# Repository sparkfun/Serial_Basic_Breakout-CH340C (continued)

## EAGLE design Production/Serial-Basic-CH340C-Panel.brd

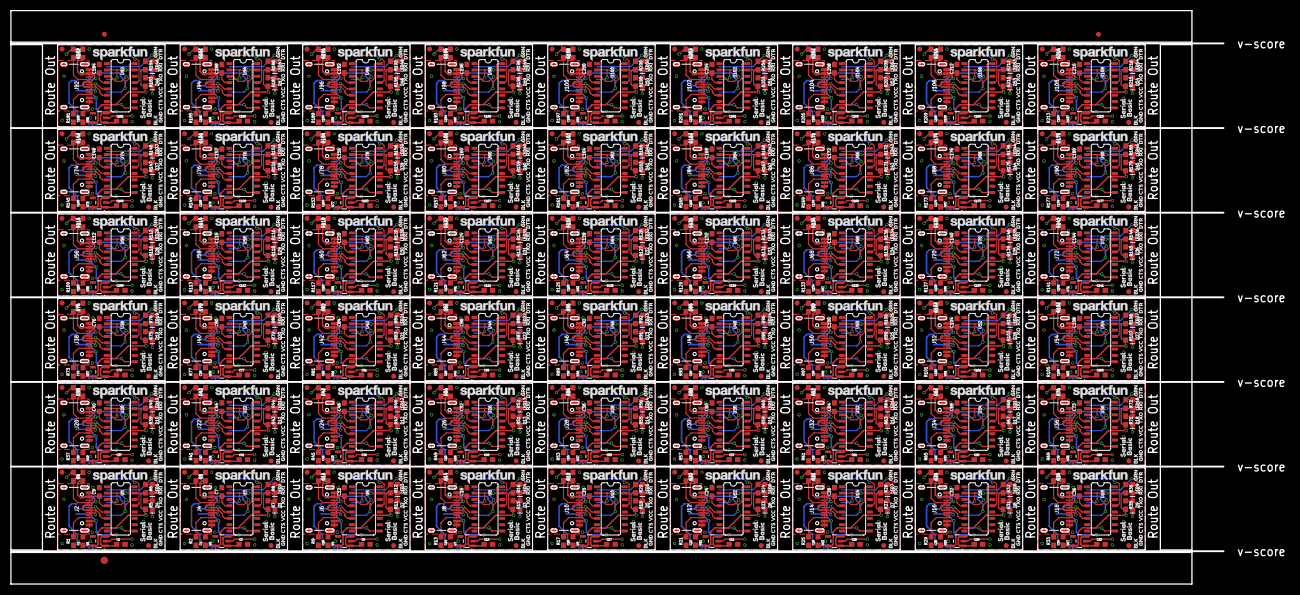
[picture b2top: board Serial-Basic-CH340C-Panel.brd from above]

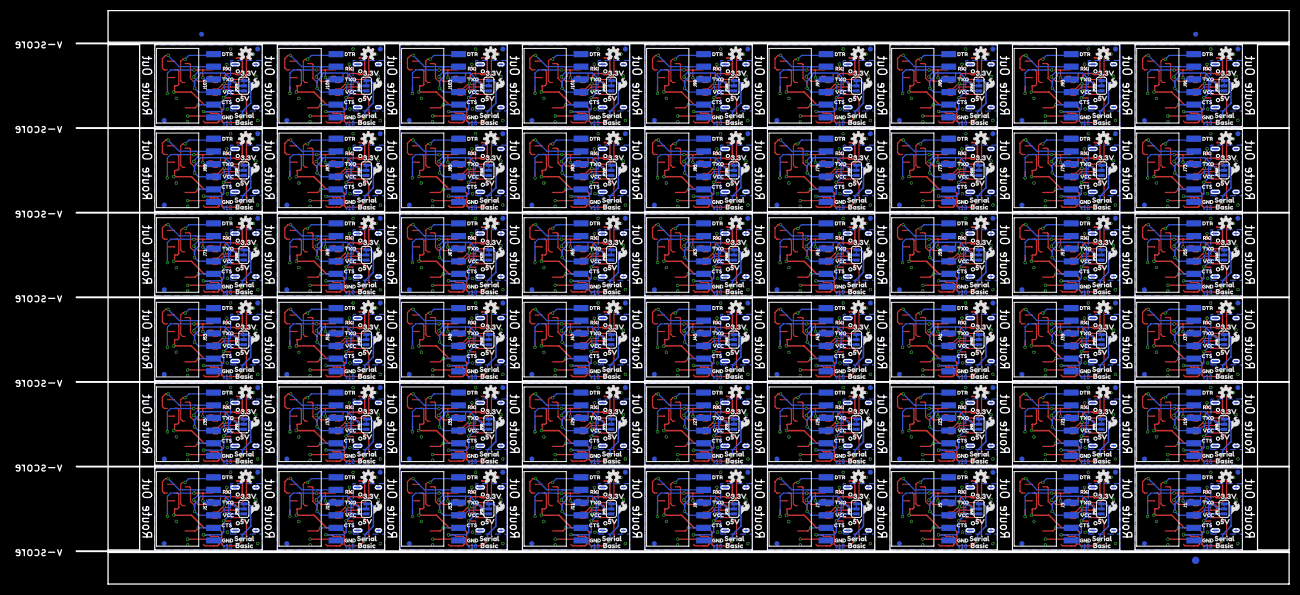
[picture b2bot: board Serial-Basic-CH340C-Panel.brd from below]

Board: 2 copper layers, 243.8 x 115.3 mm, 2274 parts (867 on the bottom side), 864 nets.

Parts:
C1, C2, C3, C4, C8, C10, C13, C14, C17, C18, C21, C22, C25, C26, C29, C30, C33, C34, C37, C38, C41, C42, C45, C46, C49, C50, C53, C54, C57, C58, C61, C62, C65, C66, C69, C70, C73, C74, C77, C78, C81, C82, C85, C86, C89, C90, C93, C94, C97, C98, C101, C102, C105, C106, C109, C110, C113, C114, C117, C118, C121, C122, C125, C126, C129, C130, C133, C134, C137, C138, C141, C142, C145, C146, C149, C150, C153, C154, C157, C158, C161, C162, C165, C166, C169, C170, C173, C174, C177, C178, C181, C182, C185, C186, C189, C190, C193, C194, C197, C198, C201, C202, C205, C206, C209, C210, C213, C214: 1.0uF; 0603
C5, C6, C11, C15, C19, C23, C27, C31, C35, C39, C43, C47, C51, C55, C59, C63, C67, C71, C75, C79, C83, C87, C91, C95, C99, C103, C107, C111, C115, C119, C123, C127, C131, C135, C139, C143, C147, C151, C155, C159, C163, C167, C171, C175, C179, C183, C187, C191, C195, C199, C203, C207, C211, C215: 0.1uF; 0603
C7, C9, C12, C16, C20, C24, C28, C32, C36, C40, C44, C48, C52, C56, C60, C64, C68, C72, C76, C80, C84, C88, C92, C96, C100, C104, C108, C112, C116, C120, C124, C128, C132, C136, C140, C144, C148, C152, C156, C160, C164, C168, C172, C176, C180, C184, C188, C192, C196, C200, C204, C208, C212, C216: 10nF; 0603
D1, D2, D3, D4, D5, D6, D7, D8, D9, D10, D11, D12, D13, D14, D15, D16, D17, D18, D19, D20, D21, D22, D23, D24, D25, D26, D27, D28, D29, D30, D31, D32, D33, D34, D35, D36, D37, D38, D39, D40, D41, D42, D43, D44, D45, D46, D47, D48, D49, D50, D51, D52, D53, D54: Yellow; LED-0603
E$1, E$2, E$3, E$4: FIDUCIAL-1X2
E$5, E$6: FIDUCIAL-1.5X3
J1, J3, J5, J7, J9, J11, J13, J15, J17, J19, J21, J23, J25, J27, J29, J31, J33, J35, J37, J39, J41, J43, J45, J47, J49, J51, J53, J55, J57, J59, J61, J63, J65, J67, J69, J71, J73, J75, J77, J79, J81, J83, J85, J87, J89, J91, J93, J95, J97, J99, J101, J103, J105, J107: 1X06-SMD-FEMALE
J2, J4, J6, J8, J10, J12, J14, J16, J18, J20, J22, J24, J26, J28, J30, J32, J34, J36, J38, J40, J42, J44, J46, J48, J50, J52, J54, J56, J58, J60, J62, J64, J66, J68, J70, J72, J74, J76, J78, J80, J82, J84, J86, J88, J90, J92, J94, J96, J98, J100, J102, J104, J106, J108: USB-C-16P
JP1, JP10, JP15, JP20, JP25, JP30, JP35, JP40, JP45, JP50, JP55, JP60, JP65, JP70, JP75, JP80, JP85, JP90, JP95, JP100, JP105, JP110, JP115, JP120, JP125, JP130, JP135, JP140, JP145, JP150, JP155, JP160, JP165, JP170, JP175, JP180, JP185, JP190, JP195, JP200, JP205, JP210, JP215, JP220, JP225, JP230, JP235, JP240, JP245, JP250, JP255, JP260, JP265, JP270: SMT-JUMPER_3_1-NC_TRACE_SILK
JP2, JP3, JP4, JP5, JP6, JP7, JP8, JP9, JP11, JP12, JP13, JP14, JP16, JP17, JP18, JP19, JP21, JP22, JP23, JP24, JP26, JP27, JP28, JP29, JP31, JP32, JP33, JP34, JP36, JP37, JP38, JP39, JP41, JP42, JP43, JP44, JP46, JP47, JP48, JP49, JP51, JP52, JP53, JP54, JP56, JP57, JP58, JP59, JP61, JP62, JP63, JP64, JP66, JP67, JP68, JP69, JP71, JP72, JP73, JP74, JP76, JP77, JP78, JP79, JP81, JP82, JP83, JP84, JP86, JP87, JP88, JP89, JP91, JP92, JP93, JP94, JP96, JP97, JP98, JP99, JP101, JP102, JP103, JP104, JP106, JP107, JP108, JP109, JP111, JP112, JP113, JP114, JP116, JP117, JP118, JP119, JP121, JP122, JP123, JP124, JP126, JP127, JP128, JP129, JP131, JP132, JP133, JP134, JP136, JP137, JP138, JP139, JP141, JP142, JP143, JP144, JP146, JP147, JP148, JP149, JP151, JP152, JP153, JP154, JP156, JP157, JP158, JP159, JP161, JP162, JP163, JP164, JP166, JP167, JP168, JP169, JP171, JP172, JP173, JP174, JP176, JP177, JP178, JP179, JP181, JP182, JP183, JP184, JP186, JP187, JP188, JP189, JP191, JP192, JP193, JP194, JP196, JP197, JP198, JP199, JP201, JP202, JP203, JP204, JP206, JP207, JP208, JP209, JP211, JP212, JP213, JP214, JP216, JP217, JP218, JP219, JP221, JP222, JP223, JP224, JP226, JP227, JP228, JP229, JP231, JP232, JP233, JP234, JP236, JP237, JP238, JP239, JP241, JP242, JP243, JP244, JP246, JP247, JP248, JP249, JP251, JP252, JP253, JP254, JP256, JP257, JP258, JP259, JP261, JP262, JP263, JP264, JP266, JP267, JP268, JP269: FIDUCIAL1X2; FIDUCIAL-1X2
LED1, LED2, LED3, LED4, LED5, LED6, LED7, LED8, LED9, LED10, LED11, LED12, LED13, LED14, LED15, LED16, LED17, LED18, LED19, LED20, LED21, LED22, LED23, LED24, LED25, LED26, LED27, LED28, LED29, LED30, LED31, LED32, LED33, LED34, LED35, LED36, LED37, LED38, LED39, LED40, LED41, LED42, LED43, LED44, LED45, LED46, LED47, LED48, LED49, LED50, LED51, LED52, LED53, LED54: GREEN; LED-0603
LOGO1, LOGO4, LOGO7, LOGO10, LOGO13, LOGO16, LOGO19, LOGO22, LOGO25, LOGO28, LOGO31, LOGO34, LOGO37, LOGO40, LOGO43, LOGO46, LOGO49, LOGO52, LOGO55, LOGO58, LOGO61, LOGO64, LOGO67, LOGO70, LOGO73, LOGO76, LOGO79, LOGO82, LOGO85, LOGO88, LOGO91, LOGO94, LOGO97, LOGO100, LOGO103, LOGO106, LOGO109, LOGO112, LOGO115, LOGO118, LOGO121, LOGO124, LOGO127, LOGO130, LOGO133, LOGO136, LOGO139, LOGO142, LOGO145, LOGO148, LOGO151, LOGO154, LOGO157, LOGO160: OSHW-LOGOS; OSHW-LOGO-S
LOGO2, LOGO5, LOGO8, LOGO11, LOGO14, LOGO17, LOGO20, LOGO23, LOGO26, LOGO29, LOGO32, LOGO35, LOGO38, LOGO41, LOGO44, LOGO47, LOGO50, LOGO53, LOGO56, LOGO59, LOGO62, LOGO65, LOGO68, LOGO71, LOGO74, LOGO77, LOGO80, LOGO83, LOGO86, LOGO89, LOGO92, LOGO95, LOGO98, LOGO101, LOGO104, LOGO107, LOGO110, LOGO113, LOGO116, LOGO119, LOGO122, LOGO125, LOGO128, LOGO131, LOGO134, LOGO137, LOGO140, LOGO143, LOGO146, LOGO149, LOGO152, LOGO155, LOGO158, LOGO161: SFE_LOGO_FLAME.1_INCH; SFE_LOGO_FLAME_.1
LOGO3, LOGO6, LOGO9, LOGO12, LOGO15, LOGO18, LOGO21, LOGO24, LOGO27, LOGO30, LOGO33, LOGO36, LOGO39, LOGO42, LOGO45, LOGO48, LOGO51, LOGO54, LOGO57, LOGO60, LOGO63, LOGO66, LOGO69, LOGO72, LOGO75, LOGO78, LOGO81, LOGO84, LOGO87, LOGO90, LOGO93, LOGO96, LOGO99, LOGO102, LOGO105, LOGO108, LOGO111, LOGO114, LOGO117, LOGO120, LOGO123, LOGO126, LOGO129, LOGO132, LOGO135, LOGO138, LOGO141, LOGO144, LOGO147, LOGO150, LOGO153, LOGO156, LOGO159, LOGO162: SFE_LOGO_NAME.1_INCH; SFE_LOGO_NAME_.1
R1, R2, R3, R4, R9, R10, R13, R14, R17, R18, R21, R22, R25, R26, R29, R30, R33, R34, R37, R38, R41, R42, R45, R46, R49, R50, R53, R54, R57, R58, R61, R62, R65, R66, R69, R70, R73, R74, R77, R78, R81, R82, R85, R86, R89, R90, R93, R94, R97, R98, R101, R102, R105, R106, R109, R110, R113, R114, R117, R118, R121, R122, R125, R126, R129, R130, R133, R134, R137, R138, R141, R142, R145, R146, R149, R150, R153, R154, R157, R158, R161, R162, R165, R166, R169, R170, R173, R174, R177, R178, R181, R182, R185, R186, R189, R190, R193, R194, R197, R198, R201, R202, R205, R206, R209, R210, R213, R214: 5.1k; 0603
R5, R6, R7, R8, R11, R12, R15, R16, R19, R20, R23, R24, R27, R28, R31, R32, R35, R36, R39, R40, R43, R44, R47, R48, R51, R52, R55, R56, R59, R60, R63, R64, R67, R68, R71, R72, R75, R76, R79, R80, R83, R84, R87, R88, R91, R92, R95, R96, R99, R100, R103, R104, R107, R108, R111, R112, R115, R116, R119, R120, R123, R124, R127, R128, R131, R132, R135, R136, R139, R140, R143, R144, R147, R148, R151, R152, R155, R156, R159, R160, R163, R164, R167, R168, R171, R172, R175, R176, R179, R180, R183, R184, R187, R188, R191, R192, R195, R196, R199, R200, R203, R204, R207, R208, R211, R212, R215, R216: 1k; 0603
U1, U2, U4, U7, U9, U11, U13, U15, U17, U19, U21, U23, U25, U27, U29, U31, U33, U35, U37, U39, U41, U43, U45, U47, U49, U51, U53, U55, U57, U59, U61, U63, U65, U67, U69, U71, U73, U75, U77, U79, U81, U83, U85, U87, U89, U91, U93, U95, U97, U99, U101, U103, U105, U107: AP2112-3.3V; SOT23-5
U3, U5, U6, U8, U10, U12, U14, U16, U18, U20, U22, U24, U26, U28, U30, U32, U34, U36, U38, U40, U42, U44, U46, U48, U50, U52, U54, U56, U58, U60, U62, U64, U66, U68, U70, U72, U74, U76, U78, U80, U82, U84, U86, U88, U90, U92, U94, U96, U98, U100, U102, U104, U106, U108: CH340C; SO016
U$1, U$14, U$28, U$37, U$48, U$57, U$68, U$77, U$88, U$97, U$108, U$117, U$128, U$137, U$148, U$157, U$168, U$177, U$188, U$197, U$208, U$217, U$228, U$237, U$248, U$257, U$268, U$277, U$288, U$297, U$308, U$317, U$328, U$337, U$348, U$357, U$368, U$377, U$388, U$397, U$408, U$417, U$428, U$437, U$448, U$457, U$468, U$477, U$488, U$497, U$508, U$517, U$528, U$537, U$548, U$557, U$568, U$577, U$588, U$597, U$608, U$617, U$628, U$637, U$648, U$657, U$668, U$677, U$688, U$697, U$708, U$717, U$728, U$737, U$748, U$757, U$768, U$777, U$788, U$797, U$808, U$817, U$828, U$837, U$848, U$857, U$868, U$877, U$888, U$897, U$908, U$917, U$928, U$937, U$948, U$957, U$968, U$977, U$988, U$997, U$1008, U$1017, U$1028, U$1037, U$1048, U$1057, U$1068, U$1077: CTS1
U$2, U$16, U$41, U$61, U$81, U$101, U$121, U$141, U$161, U$181, U$201, U$221, U$241, U$261, U$281, U$301, U$321, U$341, U$361, U$381, U$401, U$421, U$441, U$461, U$481, U$501, U$521, U$541, U$561, U$581, U$601, U$621, U$641, U$661, U$681, U$701, U$721, U$741, U$761, U$781, U$801, U$821, U$841, U$861, U$881, U$901, U$921, U$941, U$961, U$981, U$1001, U$1021, U$1041, U$1061: 3#3V8
U$3, U$22, U$42, U$62, U$82, U$102, U$122, U$142, U$162, U$182, U$202, U$222, U$242, U$262, U$282, U$302, U$322, U$342, U$362, U$382, U$402, U$422, U$442, U$462, U$482, U$502, U$522, U$542, U$562, U$582, U$602, U$622, U$642, U$662, U$682, U$702, U$722, U$742, U$762, U$782, U$802, U$822, U$842, U$862, U$882, U$902, U$922, U$942, U$962, U$982, U$1002, U$1022, U$1042, U$1062: 5V9
U$4, U$9, U$31, U$39, U$51, U$59, U$71, U$79, U$91, U$99, U$111, U$119, U$131, U$139, U$151, U$159, U$171, U$179, U$191, U$199, U$211, U$219, U$231, U$239, U$251, U$259, U$271, U$279, U$291, U$299, U$311, U$319, U$331, U$339, U$351, U$359, U$371, U$379, U$391, U$399, U$411, U$419, U$431, U$439, U$451, U$459, U$471, U$479, U$491, U$499, U$511, U$519, U$531, U$539, U$551, U$559, U$571, U$579, U$591, U$599, U$611, U$619, U$631, U$639, U$651, U$659, U$671, U$679, U$691, U$699, U$711, U$719, U$731, U$739, U$751, U$759, U$771, U$779, U$791, U$799, U$811, U$819, U$831, U$839, U$851, U$859, U$871, U$879, U$891, U$899, U$911, U$919, U$931, U$939, U$951, U$959, U$971, U$979, U$991, U$999, U$1011, U$1019, U$1031, U$1039, U$1051, U$1059, U$1071, U$1079: SERIAL0
U$5, U$12, U$29, U$35, U$49, U$55, U$69, U$75, U$89, U$95, U$109, U$115, U$129, U$135, U$149, U$155, U$169, U$175, U$189, U$195, U$209, U$215, U$229, U$235, U$249, U$255, U$269, U$275, U$289, U$295, U$309, U$315, U$329, U$335, U$349, U$355, U$369, U$375, U$389, U$395, U$409, U$415, U$429, U$435, U$449, U$455, U$469, U$475, U$489, U$495, U$509, U$515, U$529, U$535, U$549, U$555, U$569, U$575, U$589, U$595, U$609, U$615, U$629, U$635, U$649, U$655, U$669, U$675, U$689, U$695, U$709, U$715, U$729, U$735, U$749, U$755, U$769, U$775, U$789, U$795, U$809, U$815, U$829, U$835, U$849, U$855, U$869, U$875, U$889, U$895, U$909, U$915, U$929, U$935, U$949, U$955, U$969, U$975, U$989, U$995, U$1009, U$1015, U$1029, U$1035, U$1049, U$1055, U$1069, U$1075: TXO0
U$6, U$13, U$30, U$36, U$50, U$56, U$70, U$76, U$90, U$96, U$110, U$116, U$130, U$136, U$150, U$156, U$170, U$176, U$190, U$196, U$210, U$216, U$230, U$236, U$250, U$256, U$270, U$276, U$290, U$296, U$310, U$316, U$330, U$336, U$350, U$356, U$370, U$376, U$390, U$396, U$410, U$416, U$430, U$436, U$450, U$456, U$470, U$476, U$490, U$496, U$510, U$516, U$530, U$536, U$550, U$556, U$570, U$576, U$590, U$596, U$610, U$616, U$630, U$636, U$650, U$656, U$670, U$676, U$690, U$696, U$710, U$716, U$730, U$736, U$750, U$756, U$770, U$776, U$790, U$796, U$810, U$816, U$830, U$836, U$850, U$856, U$870, U$876, U$890, U$896, U$910, U$916, U$930, U$936, U$950, U$956, U$970, U$976, U$990, U$996, U$1010, U$1016, U$1030, U$1036, U$1050, U$1056, U$1070, U$1076: VCC2
U$7, U$11, U$32, U$40, U$52, U$60, U$72, U$80, U$92, U$100, U$112, U$120, U$132, U$140, U$152, U$160, U$172, U$180, U$192, U$200, U$212, U$220, U$232, U$240, U$252, U$260, U$272, U$280, U$292, U$300, U$312, U$320, U$332, U$340, U$352, U$360, U$372, U$380, U$392, U$400, U$412, U$420, U$432, U$440, U$452, U$460, U$472, U$480, U$492, U$500, U$512, U$520, U$532, U$540, U$552, U$560, U$572, U$580, U$592, U$600, U$612, U$620, U$632, U$640, U$652, U$660, U$672, U$680, U$692, U$700, U$712, U$720, U$732, U$740, U$752, U$760, U$772, U$780, U$792, U$800, U$812, U$820, U$832, U$840, U$852, U$860, U$872, U$880, U$892, U$900, U$912, U$920, U$932, U$940, U$952, U$960, U$972, U$980, U$992, U$1000, U$1012, U$1020, U$1032, U$1040, U$1052, U$1060, U$1072, U$1080: BASIC1
U$8, U$18, U$24, U$33, U$44, U$53, U$64, U$73, U$84, U$93, U$104, U$113, U$124, U$133, U$144, U$153, U$164, U$173, U$184, U$193, U$204, U$213, U$224, U$233, U$244, U$253, U$264, U$273, U$284, U$293, U$304, U$313, U$324, U$333, U$344, U$353, U$364, U$373, U$384, U$393, U$404, U$413, U$424, U$433, U$444, U$453, U$464, U$473, U$484, U$493, U$504, U$513, U$524, U$533, U$544, U$553, U$564, U$573, U$584, U$593, U$604, U$613, U$624, U$633, U$644, U$653, U$664, U$673, U$684, U$693, U$704, U$713, U$724, U$733, U$744, U$753, U$764, U$773, U$784, U$793, U$804, U$813, U$824, U$833, U$844, U$853, U$864, U$873, U$884, U$893, U$904, U$913, U$924, U$933, U$944, U$953, U$964, U$973, U$984, U$993, U$1004, U$1013, U$1024, U$1033, U$1044, U$1053, U$1064, U$1073: DTR0
U$10, U$21, U$27, U$34, U$47, U$54, U$67, U$74, U$87, U$94, U$107, U$114, U$127, U$134, U$147, U$154, U$167, U$174, U$187, U$194, U$207, U$214, U$227, U$234, U$247, U$254, U$267, U$274, U$287, U$294, U$307, U$314, U$327, U$334, U$347, U$354, U$367, U$374, U$387, U$394, U$407, U$414, U$427, U$434, U$447, U$454, U$467, U$474, U$487, U$494, U$507, U$514, U$527, U$534, U$547, U$554, U$567, U$574, U$587, U$594, U$607, U$614, U$627, U$634, U$647, U$654, U$667, U$674, U$687, U$694, U$707, U$714, U$727, U$734, U$747, U$754, U$767, U$774, U$787, U$794, U$807, U$814, U$827, U$834, U$847, U$854, U$867, U$874, U$887, U$894, U$907, U$914, U$927, U$934, U$947, U$954, U$967, U$974, U$987, U$994, U$1007, U$1014, U$1027, U$1034, U$1047, U$1054, U$1067, U$1074: RXI1
U$15, U$19, U$25, U$38, U$45, U$58, U$65, U$78, U$85, U$98, U$105, U$118, U$125, U$138, U$145, U$158, U$165, U$178, U$185, U$198, U$205, U$218, U$225, U$238, U$245, U$258, U$265, U$278, U$285, U$298, U$305, U$318, U$325, U$338, U$345, U$358, U$365, U$378, U$385, U$398, U$405, U$418, U$425, U$438, U$445, U$458, U$465, U$478, U$485, U$498, U$505, U$518, U$525, U$538, U$545, U$558, U$565, U$578, U$585, U$598, U$605, U$618, U$625, U$638, U$645, U$658, U$665, U$678, U$685, U$698, U$705, U$718, U$725, U$738, U$745, U$758, U$765, U$778, U$785, U$798, U$805, U$818, U$825, U$838, U$845, U$858, U$865, U$878, U$885, U$898, U$905, U$918, U$925, U$938, U$945, U$958, U$965, U$978, U$985, U$998, U$1005, U$1018, U$1025, U$1038, U$1045, U$1058, U$1065, U$1078: GND5
U$17, U$23, U$43, U$63, U$83, U$103, U$123, U$143, U$163, U$183, U$203, U$223, U$243, U$263, U$283, U$303, U$323, U$343, U$363, U$383, U$403, U$423, U$443, U$463, U$483, U$503, U$523, U$543, U$563, U$583, U$603, U$623, U$643, U$663, U$683, U$703, U$723, U$743, U$763, U$783, U$803, U$823, U$843, U$863, U$883, U$903, U$923, U$943, U$963, U$983, U$1003, U$1023, U$1043, U$1063: BLK6
U$20, U$26, U$46, U$66, U$86, U$106, U$126, U$146, U$166, U$186, U$206, U$226, U$246, U$266, U$286, U$306, U$326, U$346, U$366, U$386, U$406, U$426, U$446, U$466, U$486, U$506, U$526, U$546, U$566, U$586, U$606, U$626, U$646, U$666, U$686, U$706, U$726, U$746, U$766, U$786, U$806, U$826, U$846, U$866, U$886, U$906, U$926, U$946, U$966, U$986, U$1006, U$1026, U$1046, U$1066: GRN7

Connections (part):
3.3V: C2.1, JP1.3, R5.2, R6.2, U1.5
3.3V1: C4.1, JP10.3, R7.2, R8.2, U2.5
3.3V2: C10.1, JP15.3, R11.2, R12.2, U4.5
3.3V3: C14.1, JP20.3, R15.2, R16.2, U7.5
3.3V4: C18.1, JP25.3, R19.2, R20.2, U9.5
3.3V5: C22.1, JP30.3, R23.2, R24.2, U11.5
3.3V6: C26.1, JP35.3, R27.2, R28.2, U13.5
3.3V7: C30.1, JP40.3, R31.2, R32.2, U15.5
3.3V8: C34.1, JP45.3, R35.2, R36.2, U17.5
3.3V9: C38.1, JP50.3, R39.2, R40.2, U19.5
3.3V10: C42.1, JP55.3, R43.2, R44.2, U21.5
3.3V11: C46.1, JP60.3, R47.2, R48.2, U23.5
3.3V12: C50.1, JP65.3, R51.2, R52.2, U25.5
3.3V13: C54.1, JP70.3, R55.2, R56.2, U27.5
3.3V14: C58.1, JP75.3, R59.2, R60.2, U29.5
3.3V15: C62.1, JP80.3, R63.2, R64.2, U31.5
3.3V16: C66.1, JP85.3, R67.2, R68.2, U33.5
3.3V17: C70.1, JP90.3, R71.2, R72.2, U35.5
3.3V18: C74.1, JP95.3, R75.2, R76.2, U37.5
3.3V19: C78.1, JP100.3, R79.2, R80.2, U39.5
3.3V20: C82.1, JP105.3, R83.2, R84.2, U41.5
3.3V21: C86.1, JP110.3, R87.2, R88.2, U43.5
3.3V22: C90.1, JP115.3, R91.2, R92.2, U45.5
3.3V23: C94.1, JP120.3, R95.2, R96.2, U47.5
3.3V24: C98.1, JP125.3, R99.2, R100.2, U49.5
3.3V25: C102.1, JP130.3, R103.2, R104.2, U51.5
3.3V26: C106.1, JP135.3, R107.2, R108.2, U53.5
3.3V27: C110.1, JP140.3, R111.2, R112.2, U55.5
3.3V28: C114.1, JP145.3, R115.2, R116.2, U57.5
3.3V29: C118.1, JP150.3, R119.2, R120.2, U59.5
3.3V30: C122.1, JP155.3, R123.2, R124.2, U61.5
3.3V31: C126.1, JP160.3, R127.2, R128.2, U63.5
3.3V32: C130.1, JP165.3, R131.2, R132.2, U65.5
3.3V33: C134.1, JP170.3, R135.2, R136.2, U67.5
3.3V34: C138.1, JP175.3, R139.2, R140.2, U69.5
3.3V35: C142.1, JP180.3, R143.2, R144.2, U71.5
3.3V36: C146.1, JP185.3, R147.2, R148.2, U73.5
3.3V37: C150.1, JP190.3, R151.2, R152.2, U75.5
3.3V38: C154.1, JP195.3, R155.2, R156.2, U77.5
3.3V39: C158.1, JP200.3, R159.2, R160.2, U79.5
3.3V40: C162.1, JP205.3, R163.2, R164.2, U81.5
3.3V41: C166.1, JP210.3, R167.2, R168.2, U83.5
3.3V42: C170.1, JP215.3, R171.2, R172.2, U85.5
3.3V43: C174.1, JP220.3, R175.2, R176.2, U87.5
3.3V44: C178.1, JP225.3, R179.2, R180.2, U89.5
3.3V45: C182.1, JP230.3, R183.2, R184.2, U91.5
3.3V46: C186.1, JP235.3, R187.2, R188.2, U93.5
3.3V47: C190.1, JP240.3, R191.2, R192.2, U95.5
3.3V48: C194.1, JP245.3, R195.2, R196.2, U97.5
3.3V49: C198.1, JP250.3, R199.2, R200.2, U99.5
3.3V50: C202.1, JP255.3, R203.2, R204.2, U101.5
3.3V51: C206.1, JP260.3, R207.2, R208.2, U103.5
3.3V52: C210.1, JP265.3, R211.2, R212.2, U105.5
3.3V53: C214.1, JP270.3, R215.2, R216.2, U107.5
5V: C1.1, C5.1, J2.VBUS1, J2.VBUS2, JP1.1, U1.1, U1.3
5V1: C3.1, C6.1, J4.VBUS1, J4.VBUS2, JP10.1, U2.1, U2.3
5V2: C8.1, C11.1, J6.VBUS1, J6.VBUS2, JP15.1, U4.1, U4.3
5V3: C13.1, C15.1, J8.VBUS1, J8.VBUS2, JP20.1, U7.1, U7.3
5V4: C17.1, C19.1, J10.VBUS1, J10.VBUS2, JP25.1, U9.1, U9.3
5V5: C21.1, C23.1, J12.VBUS1, J12.VBUS2, JP30.1, U11.1, U11.3
5V6: C25.1, C27.1, J14.VBUS1, J14.VBUS2, JP35.1, U13.1, U13.3
5V7: C29.1, C31.1, J16.VBUS1, J16.VBUS2, JP40.1, U15.1, U15.3
5V8: C33.1, C35.1, J18.VBUS1, J18.VBUS2, JP45.1, U17.1, U17.3
5V9: C37.1, C39.1, J20.VBUS1, J20.VBUS2, JP50.1, U19.1, U19.3
5V10: C41.1, C43.1, J22.VBUS1, J22.VBUS2, JP55.1, U21.1, U21.3
5V11: C45.1, C47.1, J24.VBUS1, J24.VBUS2, JP60.1, U23.1, U23.3
5V12: C49.1, C51.1, J26.VBUS1, J26.VBUS2, JP65.1, U25.1, U25.3
5V13: C53.1, C55.1, J28.VBUS1, J28.VBUS2, JP70.1, U27.1, U27.3
5V14: C57.1, C59.1, J30.VBUS1, J30.VBUS2, JP75.1, U29.1, U29.3
5V15: C61.1, C63.1, J32.VBUS1, J32.VBUS2, JP80.1, U31.1, U31.3
5V16: C65.1, C67.1, J34.VBUS1, J34.VBUS2, JP85.1, U33.1, U33.3
5V17: C69.1, C71.1, J36.VBUS1, J36.VBUS2, JP90.1, U35.1, U35.3
5V18: C73.1, C75.1, J38.VBUS1, J38.VBUS2, JP95.1, U37.1, U37.3
5V19: C77.1, C79.1, J40.VBUS1, J40.VBUS2, JP100.1, U39.1, U39.3
5V20: C81.1, C83.1, J42.VBUS1, J42.VBUS2, JP105.1, U41.1, U41.3
5V21: C85.1, C87.1, J44.VBUS1, J44.VBUS2, JP110.1, U43.1, U43.3
5V22: C89.1, C91.1, J46.VBUS1, J46.VBUS2, JP115.1, U45.1, U45.3
5V23: C93.1, C95.1, J48.VBUS1, J48.VBUS2, JP120.1, U47.1, U47.3
5V24: C97.1, C99.1, J50.VBUS1, J50.VBUS2, JP125.1, U49.1, U49.3
5V25: C101.1, C103.1, J52.VBUS1, J52.VBUS2, JP130.1, U51.1, U51.3
5V26: C105.1, C107.1, J54.VBUS1, J54.VBUS2, JP135.1, U53.1, U53.3
5V27: C109.1, C111.1, J56.VBUS1, J56.VBUS2, JP140.1, U55.1, U55.3
5V28: C113.1, C115.1, J58.VBUS1, J58.VBUS2, JP145.1, U57.1, U57.3
5V29: C117.1, C119.1, J60.VBUS1, J60.VBUS2, JP150.1, U59.1, U59.3
5V30: C121.1, C123.1, J62.VBUS1, J62.VBUS2, JP155.1, U61.1, U61.3
5V31: C125.1, C127.1, J64.VBUS1, J64.VBUS2, JP160.1, U63.1, U63.3
5V32: C129.1, C131.1, J66.VBUS1, J66.VBUS2, JP165.1, U65.1, U65.3
5V33: C133.1, C135.1, J68.VBUS1, J68.VBUS2, JP170.1, U67.1, U67.3
5V34: C137.1, C139.1, J70.VBUS1, J70.VBUS2, JP175.1, U69.1, U69.3
5V35: C141.1, C143.1, J72.VBUS1, J72.VBUS2, JP180.1, U71.1, U71.3
5V36: C145.1, C147.1, J74.VBUS1, J74.VBUS2, JP185.1, U73.1, U73.3
5V37: C149.1, C151.1, J76.VBUS1, J76.VBUS2, JP190.1, U75.1, U75.3
5V38: C153.1, C155.1, J78.VBUS1, J78.VBUS2, JP195.1, U77.1, U77.3
5V39: C157.1, C159.1, J80.VBUS1, J80.VBUS2, JP200.1, U79.1, U79.3
5V40: C161.1, C163.1, J82.VBUS1, J82.VBUS2, JP205.1, U81.1, U81.3
5V41: C165.1, C167.1, J84.VBUS1, J84.VBUS2, JP210.1, U83.1, U83.3
5V42: C169.1, C171.1, J86.VBUS1, J86.VBUS2, JP215.1, U85.1, U85.3
5V43: C173.1, C175.1, J88.VBUS1, J88.VBUS2, JP220.1, U87.1, U87.3
5V44: C177.1, C179.1, J90.VBUS1, J90.VBUS2, JP225.1, U89.1, U89.3
5V45: C181.1, C183.1, J92.VBUS1, J92.VBUS2, JP230.1, U91.1, U91.3
5V46: C185.1, C187.1, J94.VBUS1, J94.VBUS2, JP235.1, U93.1, U93.3
5V47: C189.1, C191.1, J96.VBUS1, J96.VBUS2, JP240.1, U95.1, U95.3
5V48: C193.1, C195.1, J98.VBUS1, J98.VBUS2, JP245.1, U97.1, U97.3
5V49: C197.1, C199.1, J100.VBUS1, J100.VBUS2, JP250.1, U99.1, U99.3
5V50: C201.1, C203.1, J102.VBUS1, J102.VBUS2, JP255.1, U101.1, U101.3
5V51: C205.1, C207.1, J104.VBUS1, J104.VBUS2, JP260.1, U103.1, U103.3
5V52: C209.1, C211.1, J106.VBUS1, J106.VBUS2, JP265.1, U105.1, U105.3
5V53: C213.1, C215.1, J108.VBUS1, J108.VBUS2, JP270.1, U107.1, U107.3
!CTS: J1.2, U5.9
!CTS1: J3.2, U3.9
!CTS2: J5.2, U6.9
!CTS3: J7.2, U8.9
!CTS4: J9.2, U10.9
!CTS5: J11.2, U12.9
!CTS6: J13.2, U14.9
!CTS7: J15.2, U16.9
!CTS8: J17.2, U18.9
!CTS9: J19.2, U20.9
!CTS10: J21.2, U22.9
!CTS11: J23.2, U24.9
!CTS12: J25.2, U26.9
!CTS13: J27.2, U28.9
!CTS14: J29.2, U30.9
!CTS15: J31.2, U32.9
!CTS16: J33.2, U34.9
!CTS17: J35.2, U36.9
!CTS18: J37.2, U38.9
!CTS19: J39.2, U40.9
!CTS20: J41.2, U42.9
!CTS21: J43.2, U44.9
!CTS22: J45.2, U46.9
!CTS23: J47.2, U48.9
!CTS24: J49.2, U50.9
!CTS25: J51.2, U52.9
!CTS26: J53.2, U54.9
!CTS27: J55.2, U56.9
!CTS28: J57.2, U58.9
!CTS29: J59.2, U60.9
!CTS30: J61.2, U62.9
!CTS31: J63.2, U64.9
!CTS32: J65.2, U66.9
!CTS33: J67.2, U68.9
!CTS34: J69.2, U70.9
!CTS35: J71.2, U72.9
!CTS36: J73.2, U74.9
!CTS37: J75.2, U76.9
!CTS38: J77.2, U78.9
!CTS39: J79.2, U80.9
!CTS40: J81.2, U82.9
!CTS41: J83.2, U84.9
!CTS42: J85.2, U86.9
!CTS43: J87.2, U88.9
!CTS44: J89.2, U90.9
!CTS45: J91.2, U92.9
!CTS46: J93.2, U94.9
!CTS47: J95.2, U96.9
!CTS48: J97.2, U98.9
!CTS49: J99.2, U100.9
!CTS50: J101.2, U102.9
!CTS51: J103.2, U104.9
!CTS52: J105.2, U106.9
!CTS53: J107.2, U108.9
!DTR: J1.6, U5.13
!DTR1: J3.6, U3.13
!DTR2: J5.6, U6.13
!DTR3: J7.6, U8.13
!DTR4: J9.6, U10.13
!DTR5: J11.6, U12.13
!DTR6: J13.6, U14.13
!DTR7: J15.6, U16.13
!DTR8: J17.6, U18.13
!DTR9: J19.6, U20.13
!DTR10: J21.6, U22.13
!DTR11: J23.6, U24.13
!DTR12: J25.6, U26.13
!DTR13: J27.6, U28.13
!DTR14: J29.6, U30.13
!DTR15: J31.6, U32.13
!DTR16: J33.6, U34.13
!DTR17: J35.6, U36.13
!DTR18: J37.6, U38.13
!DTR19: J39.6, U40.13
!DTR20: J41.6, U42.13
!DTR21: J43.6, U44.13
!DTR22: J45.6, U46.13
!DTR23: J47.6, U48.13
!DTR24: J49.6, U50.13
!DTR25: J51.6, U52.13
!DTR26: J53.6, U54.13
!DTR27: J55.6, U56.13
!DTR28: J57.6, U58.13
!DTR29: J59.6, U60.13
!DTR30: J61.6, U62.13
!DTR31: J63.6, U64.13
!DTR32: J65.6, U66.13
!DTR33: J67.6, U68.13
!DTR34: J69.6, U70.13
!DTR35: J71.6, U72.13
!DTR36: J73.6, U74.13
!DTR37: J75.6, U76.13
!DTR38: J77.6, U78.13
!DTR39: J79.6, U80.13
!DTR40: J81.6, U82.13
!DTR41: J83.6, U84.13
!DTR42: J85.6, U86.13
!DTR43: J87.6, U88.13
!DTR44: J89.6, U90.13
!DTR45: J91.6, U92.13
!DTR46: J93.6, U94.13
!DTR47: J95.6, U96.13
!DTR48: J97.6, U98.13
!DTR49: J99.6, U100.13
!DTR50: J101.6, U102.13
!DTR51: J103.6, U104.13
!DTR52: J105.6, U106.13
!DTR53: J107.6, U108.13
CC1: J2.A5, R4.2
CC2: J2.B5, R1.2
CC3: J4.A5, R3.2
CC4: J4.B5, R2.2
CC5: J6.A5, R10.2
CC6: J6.B5, R9.2
CC7: J8.A5, R14.2
CC8: J8.B5, R13.2
CC9: J10.A5, R18.2
CC10: J10.B5, R17.2
CC11: J12.A5, R22.2
CC12: J12.B5, R21.2
CC13: J14.A5, R26.2
CC14: J14.B5, R25.2
CC15: J16.A5, R30.2
CC16: J16.B5, R29.2
CC17: J18.A5, R34.2
CC18: J18.B5, R33.2
CC19: J20.A5, R38.2
CC20: J20.B5, R37.2
CC21: J22.A5, R42.2
CC22: J22.B5, R41.2
CC23: J24.A5, R46.2
CC24: J24.B5, R45.2
CC25: J26.A5, R50.2
CC26: J26.B5, R49.2
CC27: J28.A5, R54.2
CC28: J28.B5, R53.2
CC29: J30.A5, R58.2
CC30: J30.B5, R57.2
CC31: J32.A5, R62.2
CC32: J32.B5, R61.2
CC33: J34.A5, R66.2
CC34: J34.B5, R65.2
CC35: J36.A5, R70.2
CC36: J36.B5, R69.2
CC37: J38.A5, R74.2
CC38: J38.B5, R73.2
CC39: J40.A5, R78.2
CC40: J40.B5, R77.2
CC41: J42.A5, R82.2
CC42: J42.B5, R81.2
CC43: J44.A5, R86.2
CC44: J44.B5, R85.2
CC45: J46.A5, R90.2
CC46: J46.B5, R89.2
CC47: J48.A5, R94.2
CC48: J48.B5, R93.2
CC49: J50.A5, R98.2
CC50: J50.B5, R97.2
CC51: J52.A5, R102.2
CC52: J52.B5, R101.2
CC53: J54.A5, R106.2
CC54: J54.B5, R105.2
CC55: J56.A5, R110.2
CC56: J56.B5, R109.2
CC57: J58.A5, R114.2
CC58: J58.B5, R113.2
CC59: J60.A5, R118.2
CC60: J60.B5, R117.2
CC61: J62.A5, R122.2
CC62: J62.B5, R121.2
CC63: J64.A5, R126.2
CC64: J64.B5, R125.2
CC65: J66.A5, R130.2
CC66: J66.B5, R129.2
CC67: J68.A5, R134.2
CC68: J68.B5, R133.2
CC69: J70.A5, R138.2
CC70: J70.B5, R137.2
CC71: J72.A5, R142.2
CC72: J72.B5, R141.2
CC73: J74.A5, R146.2
CC74: J74.B5, R145.2
CC75: J76.A5, R150.2
CC76: J76.B5, R149.2
CC77: J78.A5, R154.2
CC78: J78.B5, R153.2
CC79: J80.A5, R158.2
CC80: J80.B5, R157.2
CC81: J82.A5, R162.2
CC82: J82.B5, R161.2
CC83: J84.A5, R166.2
CC84: J84.B5, R165.2
CC85: J86.A5, R170.2
CC86: J86.B5, R169.2
CC87: J88.A5, R174.2
CC88: J88.B5, R173.2
CC89: J90.A5, R178.2
CC90: J90.B5, R177.2
CC91: J92.A5, R182.2
CC92: J92.B5, R181.2
CC93: J94.A5, R186.2
CC94: J94.B5, R185.2
CC95: J96.A5, R190.2
CC96: J96.B5, R189.2
CC97: J98.A5, R194.2
CC98: J98.B5, R193.2
CC99: J100.A5, R198.2
CC100: J100.B5, R197.2
CC101: J102.A5, R202.2
CC102: J102.B5, R201.2
CC103: J104.A5, R206.2
CC104: J104.B5, R205.2
CC105: J106.A5, R210.2
CC106: J106.B5, R209.2
CC107: J108.A5, R214.2
CC108: J108.B5, R213.2
D+: J2.A6, J2.B6, U5.5
D+1: J4.A6, J4.B6, U3.5
D+2: J6.A6, J6.B6, U6.5
D+3: J8.A6, J8.B6, U8.5
D+4: J10.A6, J10.B6, U10.5
D+5: J12.A6, J12.B6, U12.5
D+6: J14.A6, J14.B6, U14.5
D+7: J16.A6, J16.B6, U16.5
D+8: J18.A6, J18.B6, U18.5
D+9: J20.A6, J20.B6, U20.5
D+10: J22.A6, J22.B6, U22.5
D+11: J24.A6, J24.B6, U24.5
D+12: J26.A6, J26.B6, U26.5
D+13: J28.A6, J28.B6, U28.5
D+14: J30.A6, J30.B6, U30.5
D+15: J32.A6, J32.B6, U32.5
D+16: J34.A6, J34.B6, U34.5
D+17: J36.A6, J36.B6, U36.5
D+18: J38.A6, J38.B6, U38.5
D+19: J40.A6, J40.B6, U40.5
D+20: J42.A6, J42.B6, U42.5
D+21: J44.A6, J44.B6, U44.5
D+22: J46.A6, J46.B6, U46.5
D+23: J48.A6, J48.B6, U48.5
D+24: J50.A6, J50.B6, U50.5
D+25: J52.A6, J52.B6, U52.5
D+26: J54.A6, J54.B6, U54.5
D+27: J56.A6, J56.B6, U56.5
D+28: J58.A6, J58.B6, U58.5
D+29: J60.A6, J60.B6, U60.5
D+30: J62.A6, J62.B6, U62.5
D+31: J64.A6, J64.B6, U64.5
D+32: J66.A6, J66.B6, U66.5
D+33: J68.A6, J68.B6, U68.5
D+34: J70.A6, J70.B6, U70.5
D+35: J72.A6, J72.B6, U72.5
D+36: J74.A6, J74.B6, U74.5
D+37: J76.A6, J76.B6, U76.5
D+38: J78.A6, J78.B6, U78.5
D+39: J80.A6, J80.B6, U80.5
D+40: J82.A6, J82.B6, U82.5
D+41: J84.A6, J84.B6, U84.5
D+42: J86.A6, J86.B6, U86.5
D+43: J88.A6, J88.B6, U88.5
D+44: J90.A6, J90.B6, U90.5
D+45: J92.A6, J92.B6, U92.5
D+46: J94.A6, J94.B6, U94.5
D+47: J96.A6, J96.B6, U96.5
D+48: J98.A6, J98.B6, U98.5
D+49: J100.A6, J100.B6, U100.5
D+50: J102.A6, J102.B6, U102.5
D+51: J104.A6, J104.B6, U104.5
D+52: J106.A6, J106.B6, U106.5
D+53: J108.A6, J108.B6, U108.5
D-: J2.A7, J2.B7, U5.6
D-1: J4.A7, J4.B7, U3.6
D-2: J6.A7, J6.B7, U6.6
D-3: J8.A7, J8.B7, U8.6
D-4: J10.A7, J10.B7, U10.6
D-5: J12.A7, J12.B7, U12.6
D-6: J14.A7, J14.B7, U14.6
D-7: J16.A7, J16.B7, U16.6
D-8: J18.A7, J18.B7, U18.6
D-9: J20.A7, J20.B7, U20.6
D-10: J22.A7, J22.B7, U22.6
D-11: J24.A7, J24.B7, U24.6
D-12: J26.A7, J26.B7, U26.6
D-13: J28.A7, J28.B7, U28.6
D-14: J30.A7, J30.B7, U30.6
D-15: J32.A7, J32.B7, U32.6
D-16: J34.A7, J34.B7, U34.6
D-17: J36.A7, J36.B7, U36.6
D-18: J38.A7, J38.B7, U38.6
D-19: J40.A7, J40.B7, U40.6
D-20: J42.A7, J42.B7, U42.6
D-21: J44.A7, J44.B7, U44.6
D-22: J46.A7, J46.B7, U46.6
D-23: J48.A7, J48.B7, U48.6
D-24: J50.A7, J50.B7, U50.6
D-25: J52.A7, J52.B7, U52.6
D-26: J54.A7, J54.B7, U54.6
D-27: J56.A7, J56.B7, U56.6
D-28: J58.A7, J58.B7, U58.6
D-29: J60.A7, J60.B7, U60.6
D-30: J62.A7, J62.B7, U62.6
D-31: J64.A7, J64.B7, U64.6
D-32: J66.A7, J66.B7, U66.6
D-33: J68.A7, J68.B7, U68.6
D-34: J70.A7, J70.B7, U70.6
D-35: J72.A7, J72.B7, U72.6
D-36: J74.A7, J74.B7, U74.6
D-37: J76.A7, J76.B7, U76.6
D-38: J78.A7, J78.B7, U78.6
D-39: J80.A7, J80.B7, U80.6
D-40: J82.A7, J82.B7, U82.6
D-41: J84.A7, J84.B7, U84.6
D-42: J86.A7, J86.B7, U86.6
D-43: J88.A7, J88.B7, U88.6
D-44: J90.A7, J90.B7, U90.6
D-45: J92.A7, J92.B7, U92.6
D-46: J94.A7, J94.B7, U94.6
D-47: J96.A7, J96.B7, U96.6
D-48: J98.A7, J98.B7, U98.6
D-49: J100.A7, J100.B7, U100.6
D-50: J102.A7, J102.B7, U102.6
D-51: J104.A7, J104.B7, U104.6
D-52: J106.A7, J106.B7, U106.6
D-53: J108.A7, J108.B7, U108.6
GND: C1.2, C2.2, C5.2, C9.2, J1.1, J2.GND, J2.GND2, R1.1, R4.1, U1.2, U5.1
GND1: C3.2, C4.2, C6.2, C7.2, J3.1, J4.GND, J4.GND2, R2.1, R3.1, U2.2, U3.1
GND2: C8.2, C10.2, C11.2, C12.2, J5.1, J6.GND, J6.GND2, R9.1, R10.1, U4.2, U6.1
GND3: C13.2, C14.2, C15.2, C16.2, J7.1, J8.GND, J8.GND2, R13.1, R14.1, U7.2, U8.1
GND4: C17.2, C18.2, C19.2, C20.2, J9.1, J10.GND, J10.GND2, R17.1, R18.1, U9.2, U10.1
GND5: C21.2, C22.2, C23.2, C24.2, J11.1, J12.GND, J12.GND2, R21.1, R22.1, U11.2, U12.1
GND6: C25.2, C26.2, C27.2, C28.2, J13.1, J14.GND, J14.GND2, R25.1, R26.1, U13.2, U14.1
GND7: C29.2, C30.2, C31.2, C32.2, J15.1, J16.GND, J16.GND2, R29.1, R30.1, U15.2, U16.1
GND8: C33.2, C34.2, C35.2, C36.2, J17.1, J18.GND, J18.GND2, R33.1, R34.1, U17.2, U18.1
GND9: C37.2, C38.2, C39.2, C40.2, J19.1, J20.GND, J20.GND2, R37.1, R38.1, U19.2, U20.1
GND10: C41.2, C42.2, C43.2, C44.2, J21.1, J22.GND, J22.GND2, R41.1, R42.1, U21.2, U22.1
GND11: C45.2, C46.2, C47.2, C48.2, J23.1, J24.GND, J24.GND2, R45.1, R46.1, U23.2, U24.1
GND12: C49.2, C50.2, C51.2, C52.2, J25.1, J26.GND, J26.GND2, R49.1, R50.1, U25.2, U26.1
GND13: C53.2, C54.2, C55.2, C56.2, J27.1, J28.GND, J28.GND2, R53.1, R54.1, U27.2, U28.1
GND14: C57.2, C58.2, C59.2, C60.2, J29.1, J30.GND, J30.GND2, R57.1, R58.1, U29.2, U30.1
GND15: C61.2, C62.2, C63.2, C64.2, J31.1, J32.GND, J32.GND2, R61.1, R62.1, U31.2, U32.1
GND16: C65.2, C66.2, C67.2, C68.2, J33.1, J34.GND, J34.GND2, R65.1, R66.1, U33.2, U34.1
GND17: C69.2, C70.2, C71.2, C72.2, J35.1, J36.GND, J36.GND2, R69.1, R70.1, U35.2, U36.1
GND18: C73.2, C74.2, C75.2, C76.2, J37.1, J38.GND, J38.GND2, R73.1, R74.1, U37.2, U38.1
GND19: C77.2, C78.2, C79.2, C80.2, J39.1, J40.GND, J40.GND2, R77.1, R78.1, U39.2, U40.1
GND20: C81.2, C82.2, C83.2, C84.2, J41.1, J42.GND, J42.GND2, R81.1, R82.1, U41.2, U42.1
GND21: C85.2, C86.2, C87.2, C88.2, J43.1, J44.GND, J44.GND2, R85.1, R86.1, U43.2, U44.1
GND22: C89.2, C90.2, C91.2, C92.2, J45.1, J46.GND, J46.GND2, R89.1, R90.1, U45.2, U46.1
GND23: C93.2, C94.2, C95.2, C96.2, J47.1, J48.GND, J48.GND2, R93.1, R94.1, U47.2, U48.1
GND24: C97.2, C98.2, C99.2, C100.2, J49.1, J50.GND, J50.GND2, R97.1, R98.1, U49.2, U50.1
GND25: C101.2, C102.2, C103.2, C104.2, J51.1, J52.GND, J52.GND2, R101.1, R102.1, U51.2, U52.1
GND26: C105.2, C106.2, C107.2, C108.2, J53.1, J54.GND, J54.GND2, R105.1, R106.1, U53.2, U54.1
GND27: C109.2, C110.2, C111.2, C112.2, J55.1, J56.GND, J56.GND2, R109.1, R110.1, U55.2, U56.1
GND28: C113.2, C114.2, C115.2, C116.2, J57.1, J58.GND, J58.GND2, R113.1, R114.1, U57.2, U58.1
GND29: C117.2, C118.2, C119.2, C120.2, J59.1, J60.GND, J60.GND2, R117.1, R118.1, U59.2, U60.1
GND30: C121.2, C122.2, C123.2, C124.2, J61.1, J62.GND, J62.GND2, R121.1, R122.1, U61.2, U62.1
GND31: C125.2, C126.2, C127.2, C128.2, J63.1, J64.GND, J64.GND2, R125.1, R126.1, U63.2, U64.1
GND32: C129.2, C130.2, C131.2, C132.2, J65.1, J66.GND, J66.GND2, R129.1, R130.1, U65.2, U66.1
GND33: C133.2, C134.2, C135.2, C136.2, J67.1, J68.GND, J68.GND2, R133.1, R134.1, U67.2, U68.1
GND34: C137.2, C138.2, C139.2, C140.2, J69.1, J70.GND, J70.GND2, R137.1, R138.1, U69.2, U70.1
GND35: C141.2, C142.2, C143.2, C144.2, J71.1, J72.GND, J72.GND2, R141.1, R142.1, U71.2, U72.1
GND36: C145.2, C146.2, C147.2, C148.2, J73.1, J74.GND, J74.GND2, R145.1, R146.1, U73.2, U74.1
GND37: C149.2, C150.2, C151.2, C152.2, J75.1, J76.GND, J76.GND2, R149.1, R150.1, U75.2, U76.1
GND38: C153.2, C154.2, C155.2, C156.2, J77.1, J78.GND, J78.GND2, R153.1, R154.1, U77.2, U78.1
GND39: C157.2, C158.2, C159.2, C160.2, J79.1, J80.GND, J80.GND2, R157.1, R158.1, U79.2, U80.1
GND40: C161.2, C162.2, C163.2, C164.2, J81.1, J82.GND, J82.GND2, R161.1, R162.1, U81.2, U82.1
GND41: C165.2, C166.2, C167.2, C168.2, J83.1, J84.GND, J84.GND2, R165.1, R166.1, U83.2, U84.1
GND42: C169.2, C170.2, C171.2, C172.2, J85.1, J86.GND, J86.GND2, R169.1, R170.1, U85.2, U86.1
GND43: C173.2, C174.2, C175.2, C176.2, J87.1, J88.GND, J88.GND2, R173.1, R174.1, U87.2, U88.1
GND44: C177.2, C178.2, C179.2, C180.2, J89.1, J90.GND, J90.GND2, R177.1, R178.1, U89.2, U90.1
GND45: C181.2, C182.2, C183.2, C184.2, J91.1, J92.GND, J92.GND2, R181.1, R182.1, U91.2, U92.1
GND46: C185.2, C186.2, C187.2, C188.2, J93.1, J94.GND, J94.GND2, R185.1, R186.1, U93.2, U94.1
GND47: C189.2, C190.2, C191.2, C192.2, J95.1, J96.GND, J96.GND2, R189.1, R190.1, U95.2, U96.1
GND48: C193.2, C194.2, C195.2, C196.2, J97.1, J98.GND, J98.GND2, R193.1, R194.1, U97.2, U98.1
GND49: C197.2, C198.2, C199.2, C200.2, J99.1, J100.GND, J100.GND2, R197.1, R198.1, U99.2, U100.1
GND50: C201.2, C202.2, C203.2, C204.2, J101.1, J102.GND, J102.GND2, R201.1, R202.1, U101.2, U102.1
GND51: C205.2, C206.2, C207.2, C208.2, J103.1, J104.GND, J104.GND2, R205.1, R206.1, U103.2, U104.1
GND52: C209.2, C210.2, C211.2, C212.2, J105.1, J106.GND, J106.GND2, R209.1, R210.1, U105.2, U106.1
GND53: C213.2, C214.2, C215.2, C216.2, J107.1, J108.GND, J108.GND2, R213.1, R214.1, U107.2, U108.1
unnamed: C9.1, U5.4
unnamed: LED2.A, R8.1
unnamed: D1.A, R7.1
unnamed: C7.1, U3.4
unnamed: LED3.A, R12.1
unnamed: D2.A, R11.1
unnamed: C12.1, U6.4
unnamed: LED4.A, R16.1
unnamed: D3.A, R15.1
unnamed: LED1.A, R6.1
unnamed: D4.A, R5.1
unnamed: C16.1, U8.4
unnamed: LED5.A, R20.1
unnamed: D5.A, R19.1
unnamed: C20.1, U10.4
unnamed: LED6.A, R24.1
unnamed: D6.A, R23.1
unnamed: C24.1, U12.4
unnamed: LED7.A, R28.1
unnamed: D7.A, R27.1
unnamed: C28.1, U14.4
unnamed: LED8.A, R32.1
unnamed: D8.A, R31.1
unnamed: C32.1, U16.4
unnamed: LED9.A, R36.1
unnamed: D9.A, R35.1
unnamed: C36.1, U18.4
unnamed: LED10.A, R40.1
unnamed: D10.A, R39.1
unnamed: C40.1, U20.4
unnamed: LED11.A, R44.1
unnamed: D11.A, R43.1
unnamed: C44.1, U22.4
unnamed: LED12.A, R48.1
unnamed: D12.A, R47.1
unnamed: C48.1, U24.4
unnamed: LED13.A, R52.1
unnamed: D13.A, R51.1
unnamed: C52.1, U26.4
unnamed: LED14.A, R56.1
unnamed: D14.A, R55.1
unnamed: C56.1, U28.4
unnamed: LED15.A, R60.1
unnamed: D15.A, R59.1
unnamed: C60.1, U30.4
unnamed: LED16.A, R64.1
unnamed: D16.A, R63.1
unnamed: C64.1, U32.4
unnamed: LED17.A, R68.1
unnamed: D17.A, R67.1
unnamed: C68.1, U34.4
unnamed: LED18.A, R72.1
unnamed: D18.A, R71.1
unnamed: C72.1, U36.4
unnamed: LED19.A, R76.1
unnamed: D19.A, R75.1
unnamed: C76.1, U38.4
unnamed: LED20.A, R80.1
unnamed: D20.A, R79.1
unnamed: C80.1, U40.4
unnamed: LED21.A, R84.1
unnamed: D21.A, R83.1
unnamed: C84.1, U42.4
unnamed: LED22.A, R88.1
unnamed: D22.A, R87.1
unnamed: C88.1, U44.4
unnamed: LED23.A, R92.1
unnamed: D23.A, R91.1
unnamed: C92.1, U46.4
unnamed: LED24.A, R96.1
unnamed: D24.A, R95.1
unnamed: C96.1, U48.4
unnamed: LED25.A, R100.1
unnamed: D25.A, R99.1
unnamed: C100.1, U50.4
unnamed: LED26.A, R104.1
unnamed: D26.A, R103.1
unnamed: C104.1, U52.4
unnamed: LED27.A, R108.1
unnamed: D27.A, R107.1
unnamed: C108.1, U54.4
unnamed: LED28.A, R112.1
unnamed: D28.A, R111.1
unnamed: C112.1, U56.4
unnamed: LED29.A, R116.1
unnamed: D29.A, R115.1
unnamed: C116.1, U58.4
unnamed: LED30.A, R120.1
unnamed: D30.A, R119.1
unnamed: C120.1, U60.4
unnamed: LED31.A, R124.1
unnamed: D31.A, R123.1
unnamed: C124.1, U62.4
unnamed: LED32.A, R128.1
unnamed: D32.A, R127.1
unnamed: C128.1, U64.4
unnamed: LED33.A, R132.1
unnamed: D33.A, R131.1
unnamed: C132.1, U66.4
unnamed: LED34.A, R136.1
unnamed: D34.A, R135.1
unnamed: C136.1, U68.4
unnamed: LED35.A, R140.1
unnamed: D35.A, R139.1
unnamed: C140.1, U70.4
unnamed: LED36.A, R144.1
unnamed: D36.A, R143.1
unnamed: C144.1, U72.4
unnamed: LED37.A, R148.1
unnamed: D37.A, R147.1
unnamed: C148.1, U74.4
unnamed: LED38.A, R152.1
unnamed: D38.A, R151.1
unnamed: C152.1, U76.4
unnamed: LED39.A, R156.1
unnamed: D39.A, R155.1
unnamed: C156.1, U78.4
unnamed: LED40.A, R160.1
unnamed: D40.A, R159.1
unnamed: C160.1, U80.4
unnamed: LED41.A, R164.1
unnamed: D41.A, R163.1
unnamed: C164.1, U82.4
unnamed: LED42.A, R168.1
unnamed: D42.A, R167.1
unnamed: C168.1, U84.4
unnamed: LED43.A, R172.1
unnamed: D43.A, R171.1
unnamed: C172.1, U86.4
unnamed: LED44.A, R176.1
unnamed: D44.A, R175.1
unnamed: C176.1, U88.4
unnamed: LED45.A, R180.1
unnamed: D45.A, R179.1
unnamed: C180.1, U90.4
unnamed: LED46.A, R184.1
unnamed: D46.A, R183.1
unnamed: C184.1, U92.4
unnamed: LED47.A, R188.1
unnamed: D47.A, R187.1
unnamed: C188.1, U94.4
unnamed: LED48.A, R192.1
unnamed: D48.A, R191.1
unnamed: C192.1, U96.4
unnamed: LED49.A, R196.1
unnamed: D49.A, R195.1
unnamed: C196.1, U98.4
unnamed: LED50.A, R200.1
unnamed: D50.A, R199.1
unnamed: C200.1, U100.4
unnamed: LED51.A, R204.1
unnamed: D51.A, R203.1
unnamed: C204.1, U102.4
unnamed: LED52.A, R208.1
unnamed: D52.A, R207.1
unnamed: C208.1, U104.4
unnamed: LED53.A, R212.1
unnamed: D53.A, R211.1
unnamed: C212.1, U106.4
unnamed: LED54.A, R216.1
unnamed: D54.A, R215.1
unnamed: C216.1, U108.4
RXI: J1.5, LED1.C, U5.3
RXI1: J3.5, LED2.C, U3.3
RXI2: J5.5, LED3.C, U6.3
RXI3: J7.5, LED4.C, U8.3
RXI4: J9.5, LED5.C, U10.3
RXI5: J11.5, LED6.C, U12.3
RXI6: J13.5, LED7.C, U14.3
RXI7: J15.5, LED8.C, U16.3
RXI8: J17.5, LED9.C, U18.3
RXI9: J19.5, LED10.C, U20.3
RXI10: J21.5, LED11.C, U22.3
RXI11: J23.5, LED12.C, U24.3
RXI12: J25.5, LED13.C, U26.3
RXI13: J27.5, LED14.C, U28.3
RXI14: J29.5, LED15.C, U30.3
RXI15: J31.5, LED16.C, U32.3
RXI16: J33.5, LED17.C, U34.3
RXI17: J35.5, LED18.C, U36.3
RXI18: J37.5, LED19.C, U38.3
RXI19: J39.5, LED20.C, U40.3
RXI20: J41.5, LED21.C, U42.3
RXI21: J43.5, LED22.C, U44.3
RXI22: J45.5, LED23.C, U46.3
RXI23: J47.5, LED24.C, U48.3
RXI24: J49.5, LED25.C, U50.3
RXI25: J51.5, LED26.C, U52.3
RXI26: J53.5, LED27.C, U54.3
RXI27: J55.5, LED28.C, U56.3
RXI28: J57.5, LED29.C, U58.3
RXI29: J59.5, LED30.C, U60.3
RXI30: J61.5, LED31.C, U62.3
RXI31: J63.5, LED32.C, U64.3
RXI32: J65.5, LED33.C, U66.3
RXI33: J67.5, LED34.C, U68.3
RXI34: J69.5, LED35.C, U70.3
RXI35: J71.5, LED36.C, U72.3
RXI36: J73.5, LED37.C, U74.3
RXI37: J75.5, LED38.C, U76.3
RXI38: J77.5, LED39.C, U78.3
RXI39: J79.5, LED40.C, U80.3
RXI40: J81.5, LED41.C, U82.3
RXI41: J83.5, LED42.C, U84.3
RXI42: J85.5, LED43.C, U86.3
RXI43: J87.5, LED44.C, U88.3
RXI44: J89.5, LED45.C, U90.3
RXI45: J91.5, LED46.C, U92.3
RXI46: J93.5, LED47.C, U94.3
RXI47: J95.5, LED48.C, U96.3
RXI48: J97.5, LED49.C, U98.3
RXI49: J99.5, LED50.C, U100.3
RXI50: J101.5, LED51.C, U102.3
RXI51: J103.5, LED52.C, U104.3
RXI52: J105.5, LED53.C, U106.3
RXI53: J107.5, LED54.C, U108.3
SHLD: J2.SHLD1, J2.SHLD2, J2.SHLD3, J2.SHLD4, J2.SHLD5, J2.SHLD6, J2.SHLD7, J2.SHLD8
SHLD1: J4.SHLD1, J4.SHLD2, J4.SHLD3, J4.SHLD4, J4.SHLD5, J4.SHLD6, J4.SHLD7, J4.SHLD8
SHLD2: J6.SHLD1, J6.SHLD2, J6.SHLD3, J6.SHLD4, J6.SHLD5, J6.SHLD6, J6.SHLD7, J6.SHLD8
SHLD3: J8.SHLD1, J8.SHLD2, J8.SHLD3, J8.SHLD4, J8.SHLD5, J8.SHLD6, J8.SHLD7, J8.SHLD8
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
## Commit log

2018-11-12 Updating libraries, tidied up schematic, deleted unneccessary files, adding readme outline
2018-11-12 Mispelled "plug"
2018-12-06 Add Hardware Folder Path
